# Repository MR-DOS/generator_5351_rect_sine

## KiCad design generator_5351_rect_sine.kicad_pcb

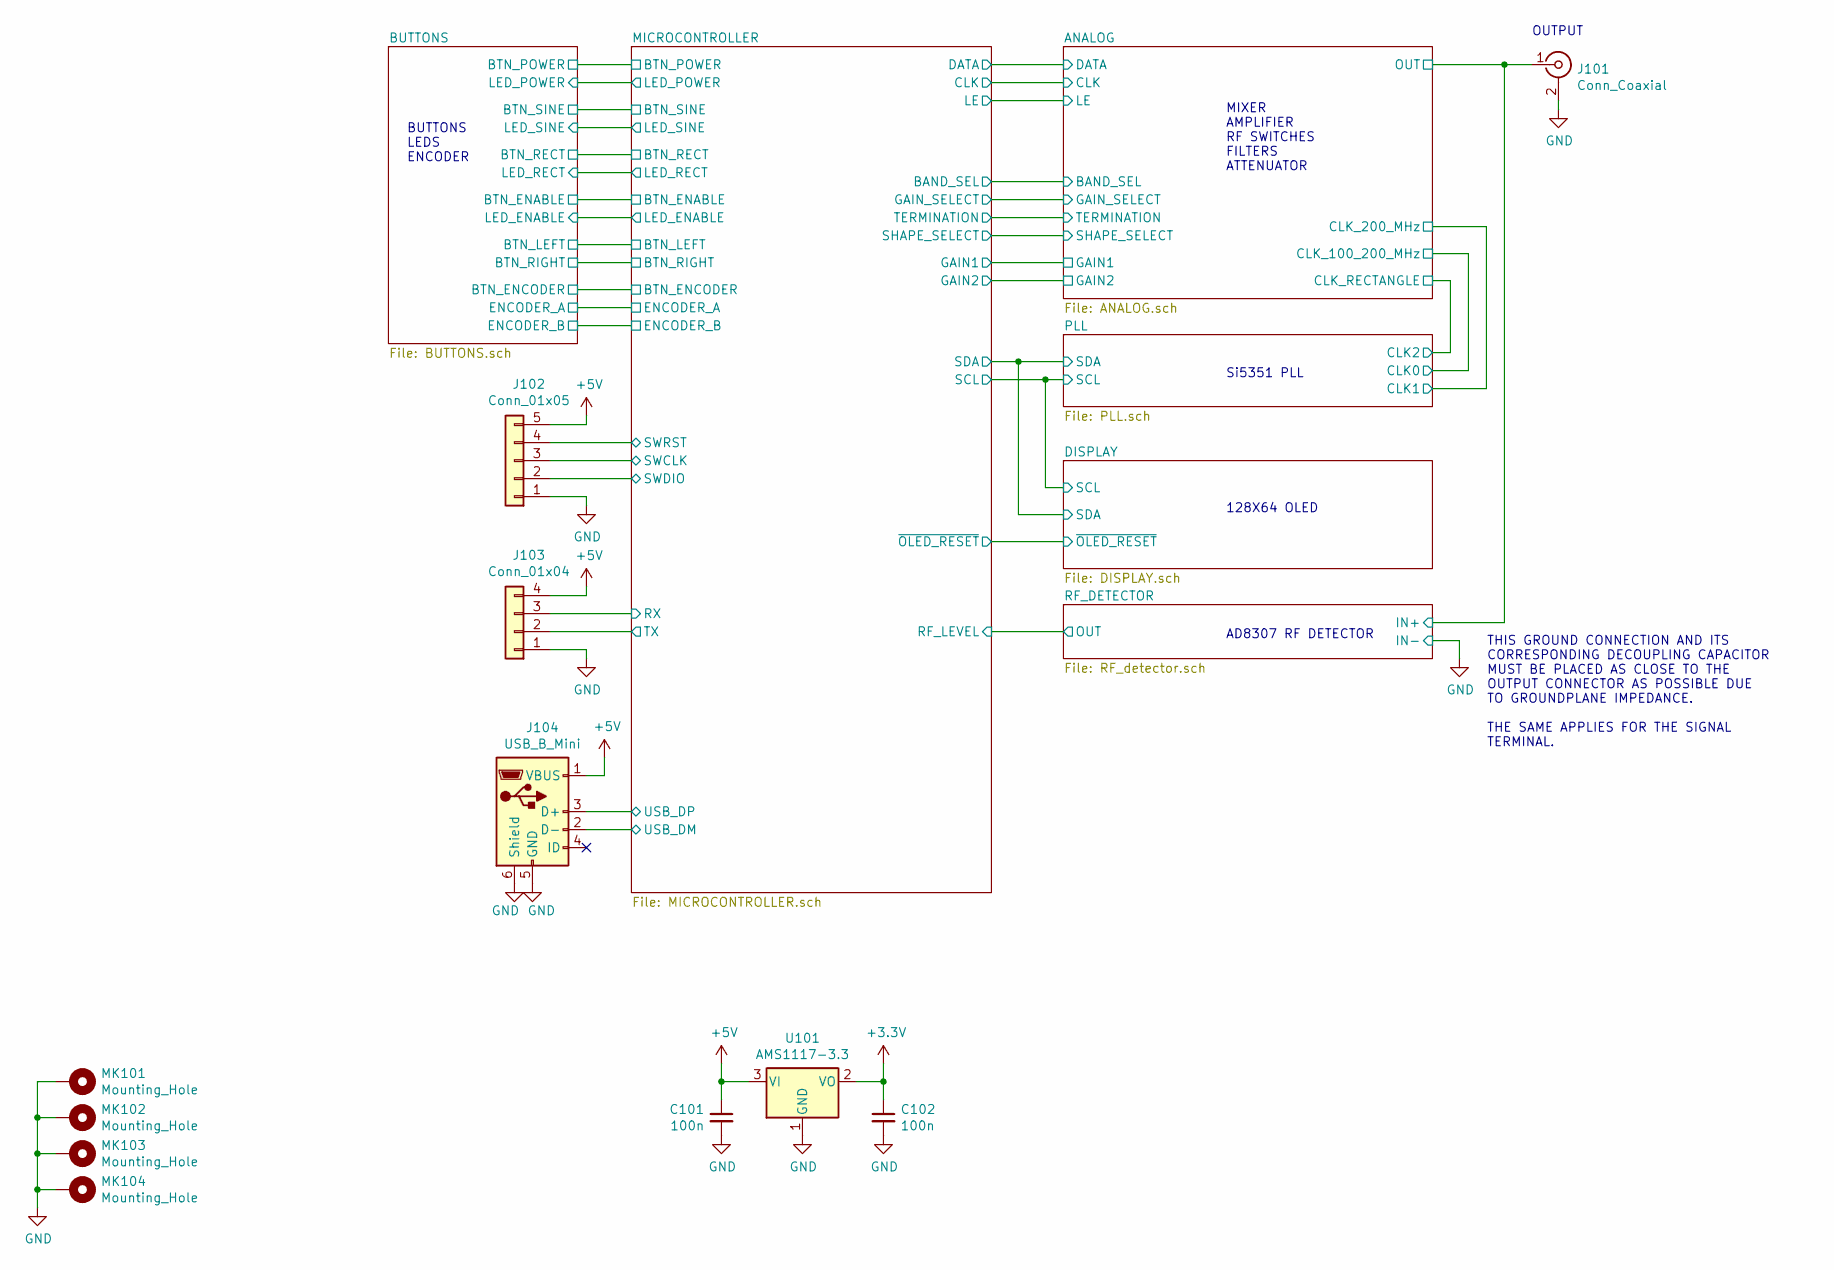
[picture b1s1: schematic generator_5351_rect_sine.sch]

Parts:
C101, C102: 100n; C_0805_2012Metric_Pad1.33x1.40mm_HandSolder
J101: Conn_Coaxial; Molex_SMA_Jack_Edge_Mount_Chinese
J102: Conn_01x05; JST_VH_B5PS-VH_1x05_P3.96mm_Horizontal
J103: Conn_01x04; JST_VH_B4PS-VH_1x04_P3.96mm_Horizontal
J104: USB_B_Mini; USB_Mini-B_Lumberg_2486_01_Horizontal
MK101, MK102, MK103, MK104: Mounting_Hole; MountingHole_3.2mm_M3_Pad
U101: AMS1117-3.3; SOT-223-3_TabPin2

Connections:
+5V: C101.1, J102.5, J103.4, J104.1 (VBUS), U101.3 (VI); also elsewhere on the board
/MICROCONTROLLER/RX: J103.3; also elsewhere on the board
/MICROCONTROLLER/SWCLK: J102.3; also elsewhere on the board
/MICROCONTROLLER/SWDIO: J102.2; also elsewhere on the board
/MICROCONTROLLER/SWRST: J102.4; also elsewhere on the board
/MICROCONTROLLER/TX: J103.2; also elsewhere on the board
/MICROCONTROLLER/USB_DM: J104.2 (D-); also elsewhere on the board
/MICROCONTROLLER/USB_DP: J104.3 (D+); also elsewhere on the board
/RF_DETECTOR/IN+: J101.1 (In); also elsewhere on the board
SW_GND: C101.2, C102.2, J101.2 (Ext), J102.1, J103.1, J104.5 (GND), J104.6 (Shield), MK101.1, MK102.1, MK103.1, MK104.1, U101.1 (GND); also elsewhere on the board

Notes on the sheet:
THIS GROUND CONNECTION AND ITS CORRESPONDING DECOUPLING CAPACITOR MUST BE PLACED AS CLOSE TO THE OUTPUT CONNECTOR AS POSSIBLE DUE TO GROUNDPLANE IMPEDANCE. THE SAME APPLIES FOR THE SIGNAL TERMINAL.
MIXER AMPLIFIER RF SWITCHES FILTERS ATTENUATOR
Si5351 PLL
128X64 OLED
AD8307 RF DETECTOR
OUTPUT
BUTTONS LEDS ENCODER

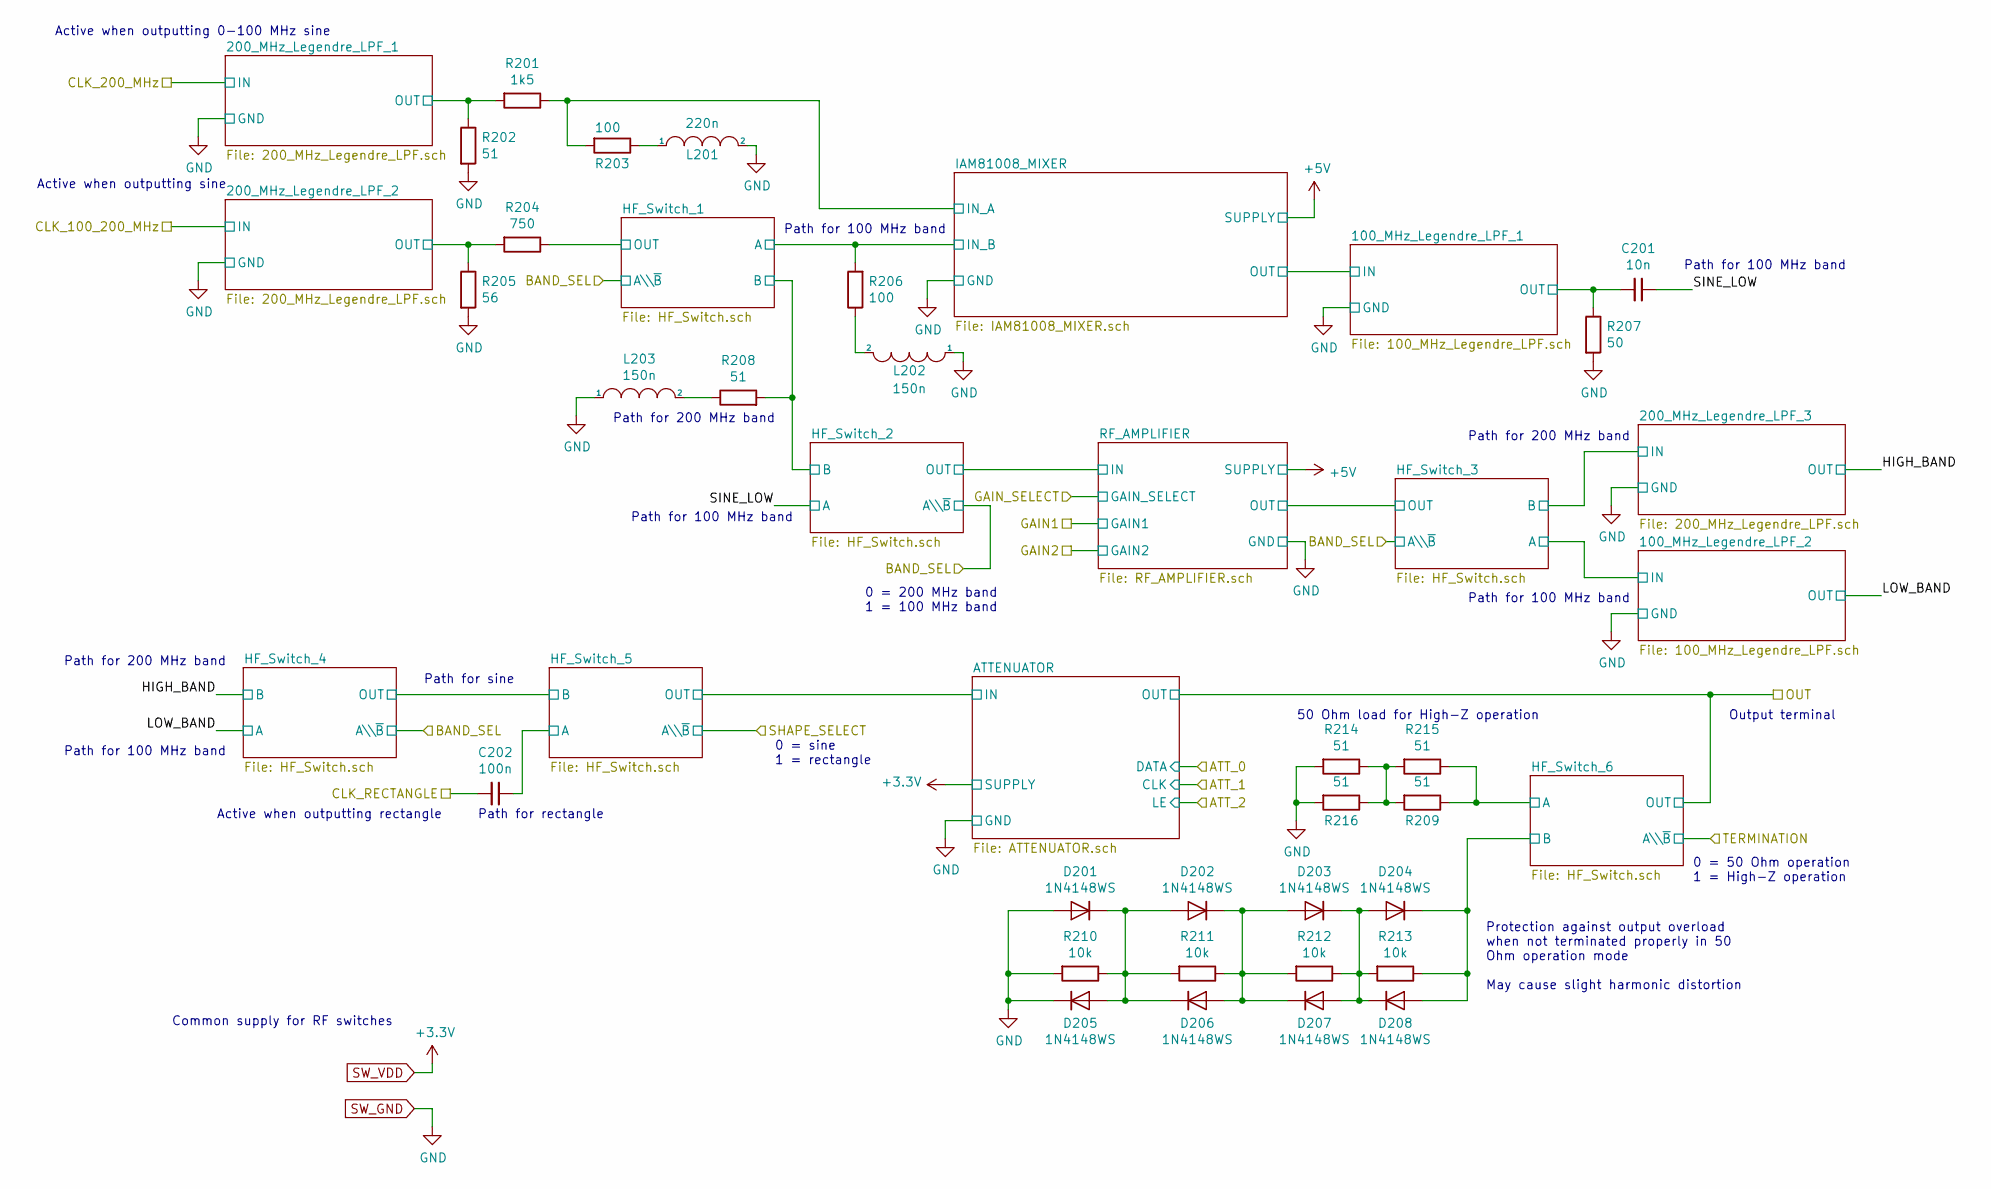
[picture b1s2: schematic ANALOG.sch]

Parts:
C201: 10n; C_0805_2012Metric_Pad1.33x1.40mm_HandSolder
C202: 100n; C_0805_2012Metric_Pad1.33x1.40mm_HandSolder
D201, D202, D203, D204, D205, D206, D207, D208: 1N4148WS; D_SOD-323
L201: 220n; L_0805_2012Metric_Pad1.33x1.40mm_HandSolder
L202, L203: 150n; L_0805_2012Metric_Pad1.33x1.40mm_HandSolder
R201: 1k5; R_0805_2012Metric_Pad1.33x1.40mm_HandSolder
R202, R208, R209, R214, R215, R216: 51; R_0805_2012Metric_Pad1.33x1.40mm_HandSolder
R203, R206: 100; R_0805_2012Metric_Pad1.33x1.40mm_HandSolder
R204: 750; R_0805_2012Metric_Pad1.33x1.40mm_HandSolder
R205: 56; R_0805_2012Metric_Pad1.33x1.40mm_HandSolder
R207: 50; R_0805_2012Metric_Pad1.33x1.40mm_HandSolder
R210, R211, R212, R213: 10k; R_0805_2012Metric_Pad1.33x1.40mm_HandSolder

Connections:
/ANALOG/100_MHz_Legendre_LPF_1/OUT: C201.2, R207.1; also elsewhere on the board
/ANALOG/200_MHz_Legendre_LPF_1/OUT: R201.2, R202.1; also elsewhere on the board
/ANALOG/200_MHz_Legendre_LPF_2/OUT: R204.2, R205.1; also elsewhere on the board
/ANALOG/HF_Switch_1/A: R206.2; also elsewhere on the board
/ANALOG/HF_Switch_1/B: R208.2; also elsewhere on the board
/ANALOG/HF_Switch_1/OUT: R204.1; also elsewhere on the board
/ANALOG/HF_Switch_5/A: C202.1; also elsewhere on the board
/ANALOG/HF_Switch_6/A: R209.1, R215.1; also elsewhere on the board
/ANALOG/HF_Switch_6/B: D204.1 (K), D208.2 (A), R213.1; also elsewhere on the board
/ANALOG/IAM81008_MIXER/IN_A: R201.1, R203.2; also elsewhere on the board
/ANALOG/SINE_LOW: C201.1; also elsewhere on the board
/PLL/CLK2: C202.2; also elsewhere on the board
unnamed: D201.1 (K), D202.2 (A), D205.2 (A), D206.1 (K), R210.1, R211.2
unnamed: D202.1 (K), D203.2 (A), D206.2 (A), D207.1 (K), R211.1, R212.2
unnamed: D203.1 (K), D204.2 (A), D207.2 (A), D208.1 (K), R212.1, R213.2
unnamed: L201.1, R203.1
unnamed: L202.2, R206.1
unnamed: L203.2, R208.1
unnamed: R209.2, R214.1, R215.2, R216.1
SW_GND: D201.2 (A), D205.1 (K), L201.2, L202.1, L203.1, R202.2, R205.2, R207.2, R210.2, R214.2, R216.2; also elsewhere on the board

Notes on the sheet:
Path for 100 MHz band
Path for 200 MHz band
Common supply for RF switches
Active when outputting 0-100 MHz sine
Active when outputting sine
0 = sine 1 = rectangle
Path for sine
Path for rectangle
Protection against output overload when not terminated properly in 50 Ohm operation mode May cause slight harmonic distortion
50 Ohm load for High-Z operation
0 = 50 Ohm operation 1 = High-Z operation
Output terminal
0 = 200 MHz band 1 = 100 MHz band
Active when outputting rectangle

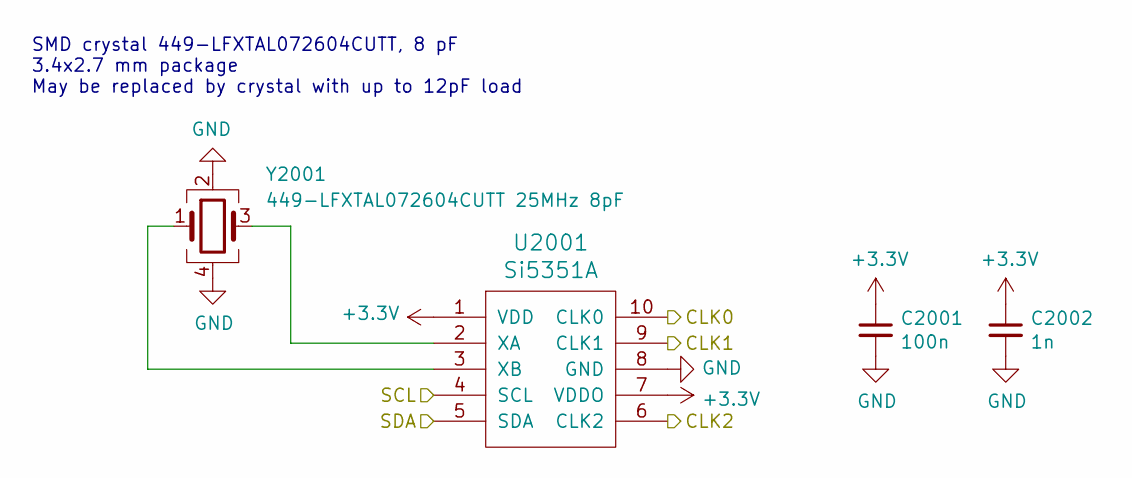
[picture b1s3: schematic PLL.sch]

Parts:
C2001: 100n; C_0805_2012Metric_Pad1.33x1.40mm_HandSolder
C2002: 1n; C_0805_2012Metric_Pad1.33x1.40mm_HandSolder
U2001: Si5351A; MSOP-10_3x3mm_P0.5mm
Y2001: 449-LFXTAL072604CUTT 25MHz 8pF; Crystal_SMD_3225-4Pin_3.2x2.5mm_HandSoldering

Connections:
/DISPLAY/SCL: U2001.4 (SCL); also elsewhere on the board
/DISPLAY/SDA: U2001.5 (SDA); also elsewhere on the board
/PLL/CLK0: U2001.10 (CLK0); also elsewhere on the board
/PLL/CLK1: U2001.9 (CLK1); also elsewhere on the board
/PLL/CLK2: U2001.6 (CLK2); also elsewhere on the board
unnamed: U2001.2 (XA), Y2001.3
unnamed: U2001.3 (XB), Y2001.1
SW_GND: C2001.2, C2002.2, U2001.8 (GND), Y2001.2, Y2001.4; also elsewhere on the board

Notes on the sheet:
SMD crystal 449-LFXTAL072604CUTT, 8 pF 3.4x2.7 mm package May be replaced by crystal with up to 12pF load

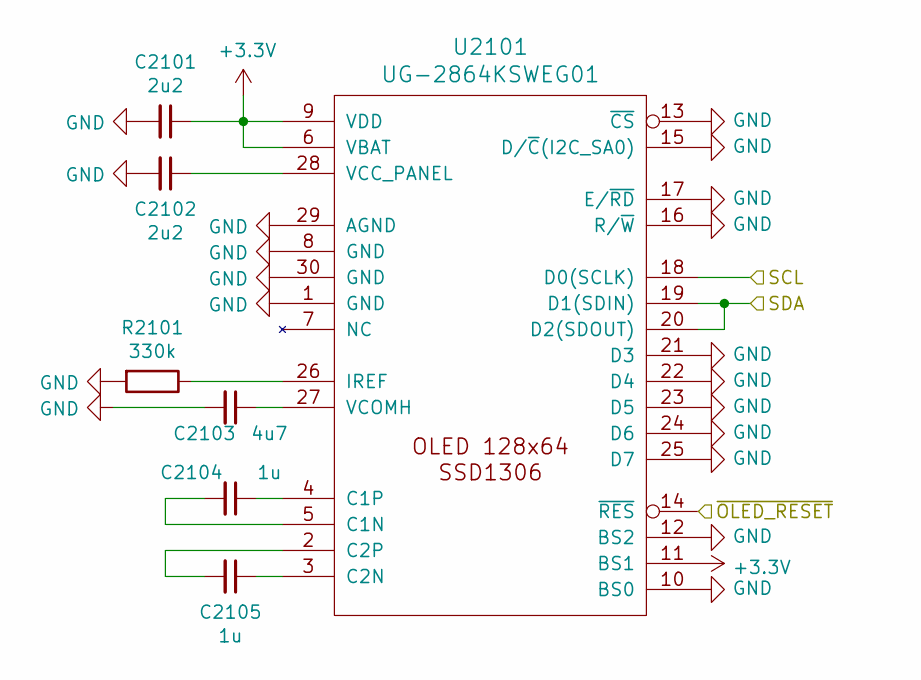
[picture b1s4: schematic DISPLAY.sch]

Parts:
C2101, C2102: 2u2; C_0805_2012Metric_Pad1.33x1.40mm_HandSolder
C2103: 4u7; C_0805_2012Metric_Pad1.33x1.40mm_HandSolder
C2104, C2105: 1u; C_0805_2012Metric_Pad1.33x1.40mm_HandSolder
R2101: 330k; R_0805_2012Metric_Pad1.33x1.40mm_HandSolder
U2101: UG-2864KSWEG01

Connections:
/DISPLAY/SCL: U2101.18 (D0(SCLK)); also elsewhere on the board
/DISPLAY/SDA: U2101.19 (D1(SDIN)), U2101.20 (D2(SDOUT)); also elsewhere on the board
/DISPLAY/~OLED_RESET: U2101.14 (~RES); also elsewhere on the board
unnamed: C2102.1, U2101.28 (VCC_PANEL)
unnamed: C2103.1, U2101.27 (VCOMH)
unnamed: C2104.1, U2101.4 (C1P)
unnamed: C2104.2, U2101.5 (C1N)
unnamed: C2105.1, U2101.3 (C2N)
unnamed: C2105.2, U2101.2 (C2P)
unnamed: R2101.1, U2101.26 (IREF)
SW_GND: C2101.2, C2102.2, C2103.2, R2101.2, U2101.1 (GND), U2101.8 (GND), U2101.10 (BS0), U2101.12 (BS2), U2101.13 (~CS), U2101.15 (D/~C~(I2C_SA0)), U2101.16 (R/~W), U2101.17 (E/~RD), U2101.21 (D3), U2101.22 (D4), U2101.23 (D5), U2101.24 (D6), U2101.25 (D7), U2101.29 (AGND), U2101.30 (GND); also elsewhere on the board

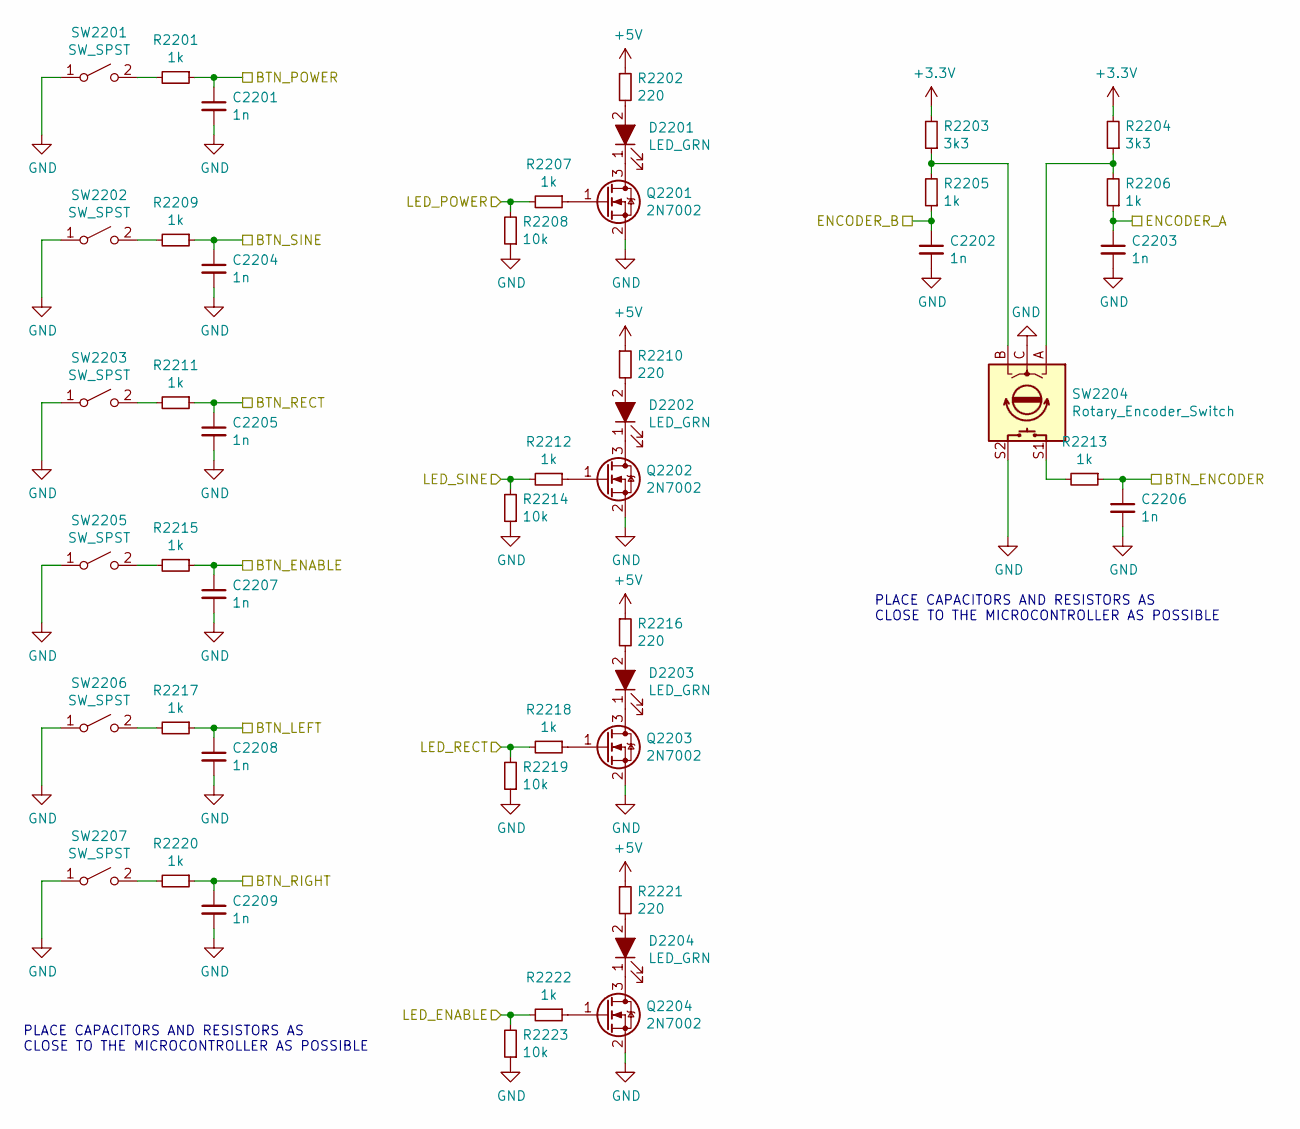
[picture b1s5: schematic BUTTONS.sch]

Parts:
C2201, C2202, C2203, C2204, C2205, C2206, C2207, C2208, C2209: 1n; C_0805_2012Metric_Pad1.33x1.40mm_HandSolder
D2201, D2202, D2203, D2204: LED_GRN; C_0603_1608Metric_Pad1.05x0.95mm_HandSolder
Q2201, Q2202, Q2203, Q2204: 2N7002; SOT-23_Handsoldering
R2201, R2205, R2206, R2207, R2209, R2211, R2212, R2213, R2215, R2217, R2218, R2220, R2222: 1k; R_0805_2012Metric_Pad1.33x1.40mm_HandSolder
R2202, R2210, R2216, R2221: 220; R_0805_2012Metric_Pad1.33x1.40mm_HandSolder
R2203, R2204: 3k3; R_0805_2012Metric_Pad1.33x1.40mm_HandSolder
R2208, R2214, R2219, R2223: 10k; R_0805_2012Metric_Pad1.33x1.40mm_HandSolder
SW2201, SW2202, SW2203, SW2205, SW2206, SW2207: SW_SPST; SW_SPST_TL3342
SW2204: Rotary_Encoder_Switch; RotaryEncoder_Alps_EC11E-Switch_Vertical_H20mm

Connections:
+5V: R2202.1, R2210.1, R2216.1, R2221.1; also elsewhere on the board
/BUTTONS/BTN_ENABLE: C2207.1, R2215.1; also elsewhere on the board
/BUTTONS/BTN_ENCODER: C2206.1, R2213.1; also elsewhere on the board
/BUTTONS/BTN_LEFT: C2208.1, R2217.1; also elsewhere on the board
/BUTTONS/BTN_POWER: C2201.1, R2201.1; also elsewhere on the board
/BUTTONS/BTN_RECT: C2205.1, R2211.1; also elsewhere on the board
/BUTTONS/BTN_RIGHT: C2209.1, R2220.1; also elsewhere on the board
/BUTTONS/BTN_SINE: C2204.1, R2209.1; also elsewhere on the board
/BUTTONS/ENCODER_A: C2203.1, R2206.1; also elsewhere on the board
/BUTTONS/ENCODER_B: C2202.1, R2205.1; also elsewhere on the board
/BUTTONS/LED_ENABLE: R2222.2, R2223.2; also elsewhere on the board
/BUTTONS/LED_POWER: R2207.2, R2208.2; also elsewhere on the board
/BUTTONS/LED_RECT: R2218.2, R2219.2; also elsewhere on the board
/BUTTONS/LED_SINE: R2212.2, R2214.2; also elsewhere on the board
unnamed: D2201.1 (K), Q2201.3 (D)
unnamed: D2201.2 (A), R2202.2
unnamed: D2202.1 (K), Q2202.3 (D)
unnamed: D2202.2 (A), R2210.2
unnamed: D2203.1 (K), Q2203.3 (D)
unnamed: D2203.2 (A), R2216.2
unnamed: D2204.1 (K), Q2204.3 (D)
unnamed: D2204.2 (A), R2221.2
unnamed: Q2201.1 (G), R2207.1
unnamed: Q2202.1 (G), R2212.1
unnamed: Q2203.1 (G), R2218.1
unnamed: Q2204.1 (G), R2222.1
unnamed: R2201.2, SW2201.2 (B)
unnamed: R2203.1, R2205.2, SW2204.B
unnamed: R2204.1, R2206.2, SW2204.A
unnamed: R2209.2, SW2202.2 (B)
unnamed: R2211.2, SW2203.2 (B)
unnamed: R2213.2, SW2204.S1
unnamed: R2215.2, SW2205.2 (B)
unnamed: R2217.2, SW2206.2 (B)
unnamed: R2220.2, SW2207.2 (B)
SW_GND: C2201.2, C2202.2, C2203.2, C2204.2, C2205.2, C2206.2, C2207.2, C2208.2, C2209.2, Q2201.2 (S), Q2202.2 (S), Q2203.2 (S), Q2204.2 (S), R2208.1, R2214.1, R2219.1, R2223.1, SW2201.1 (A), SW2202.1 (A), SW2203.1 (A), SW2204.C, SW2204.S2, SW2205.1 (A), SW2206.1 (A), SW2207.1 (A); also elsewhere on the board

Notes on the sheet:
PLACE CAPACITORS AND RESISTORS AS CLOSE TO THE MICROCONTROLLER AS POSSIBLE

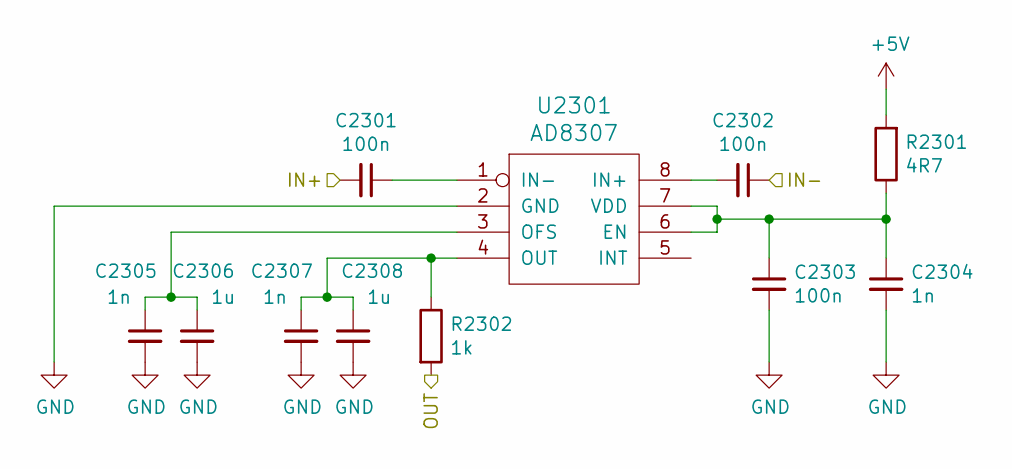
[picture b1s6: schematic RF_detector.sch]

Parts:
C2301, C2302, C2303: 100n; C_0805_2012Metric_Pad1.33x1.40mm_HandSolder
C2304, C2305, C2307: 1n; C_0805_2012Metric_Pad1.33x1.40mm_HandSolder
C2306, C2308: 1u; C_0805_2012Metric_Pad1.33x1.40mm_HandSolder
R2301: 4R7; R_0805_2012Metric_Pad1.33x1.40mm_HandSolder
R2302: 1k; R_0805_2012Metric_Pad1.33x1.40mm_HandSolder
U2301: AD8307; SOIC-8_3.9x4.9mm_P1.27mm

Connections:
+5V: R2301.2; also elsewhere on the board
/RF_DETECTOR/IN+: C2301.2; also elsewhere on the board
/RF_DETECTOR/OUT: R2302.2; also elsewhere on the board
unnamed: C2301.1, U2301.1 (IN-)
unnamed: C2302.2, U2301.8 (IN+)
unnamed: C2303.1, C2304.1, R2301.1, U2301.6 (EN), U2301.7 (VDD)
unnamed: C2305.1, C2306.1, U2301.3 (OFS)
unnamed: C2307.1, C2308.1, R2302.1, U2301.4 (OUT)
SW_GND: C2302.1, C2303.2, C2304.2, C2305.2, C2306.2, C2307.2, C2308.2, U2301.2 (GND); also elsewhere on the board

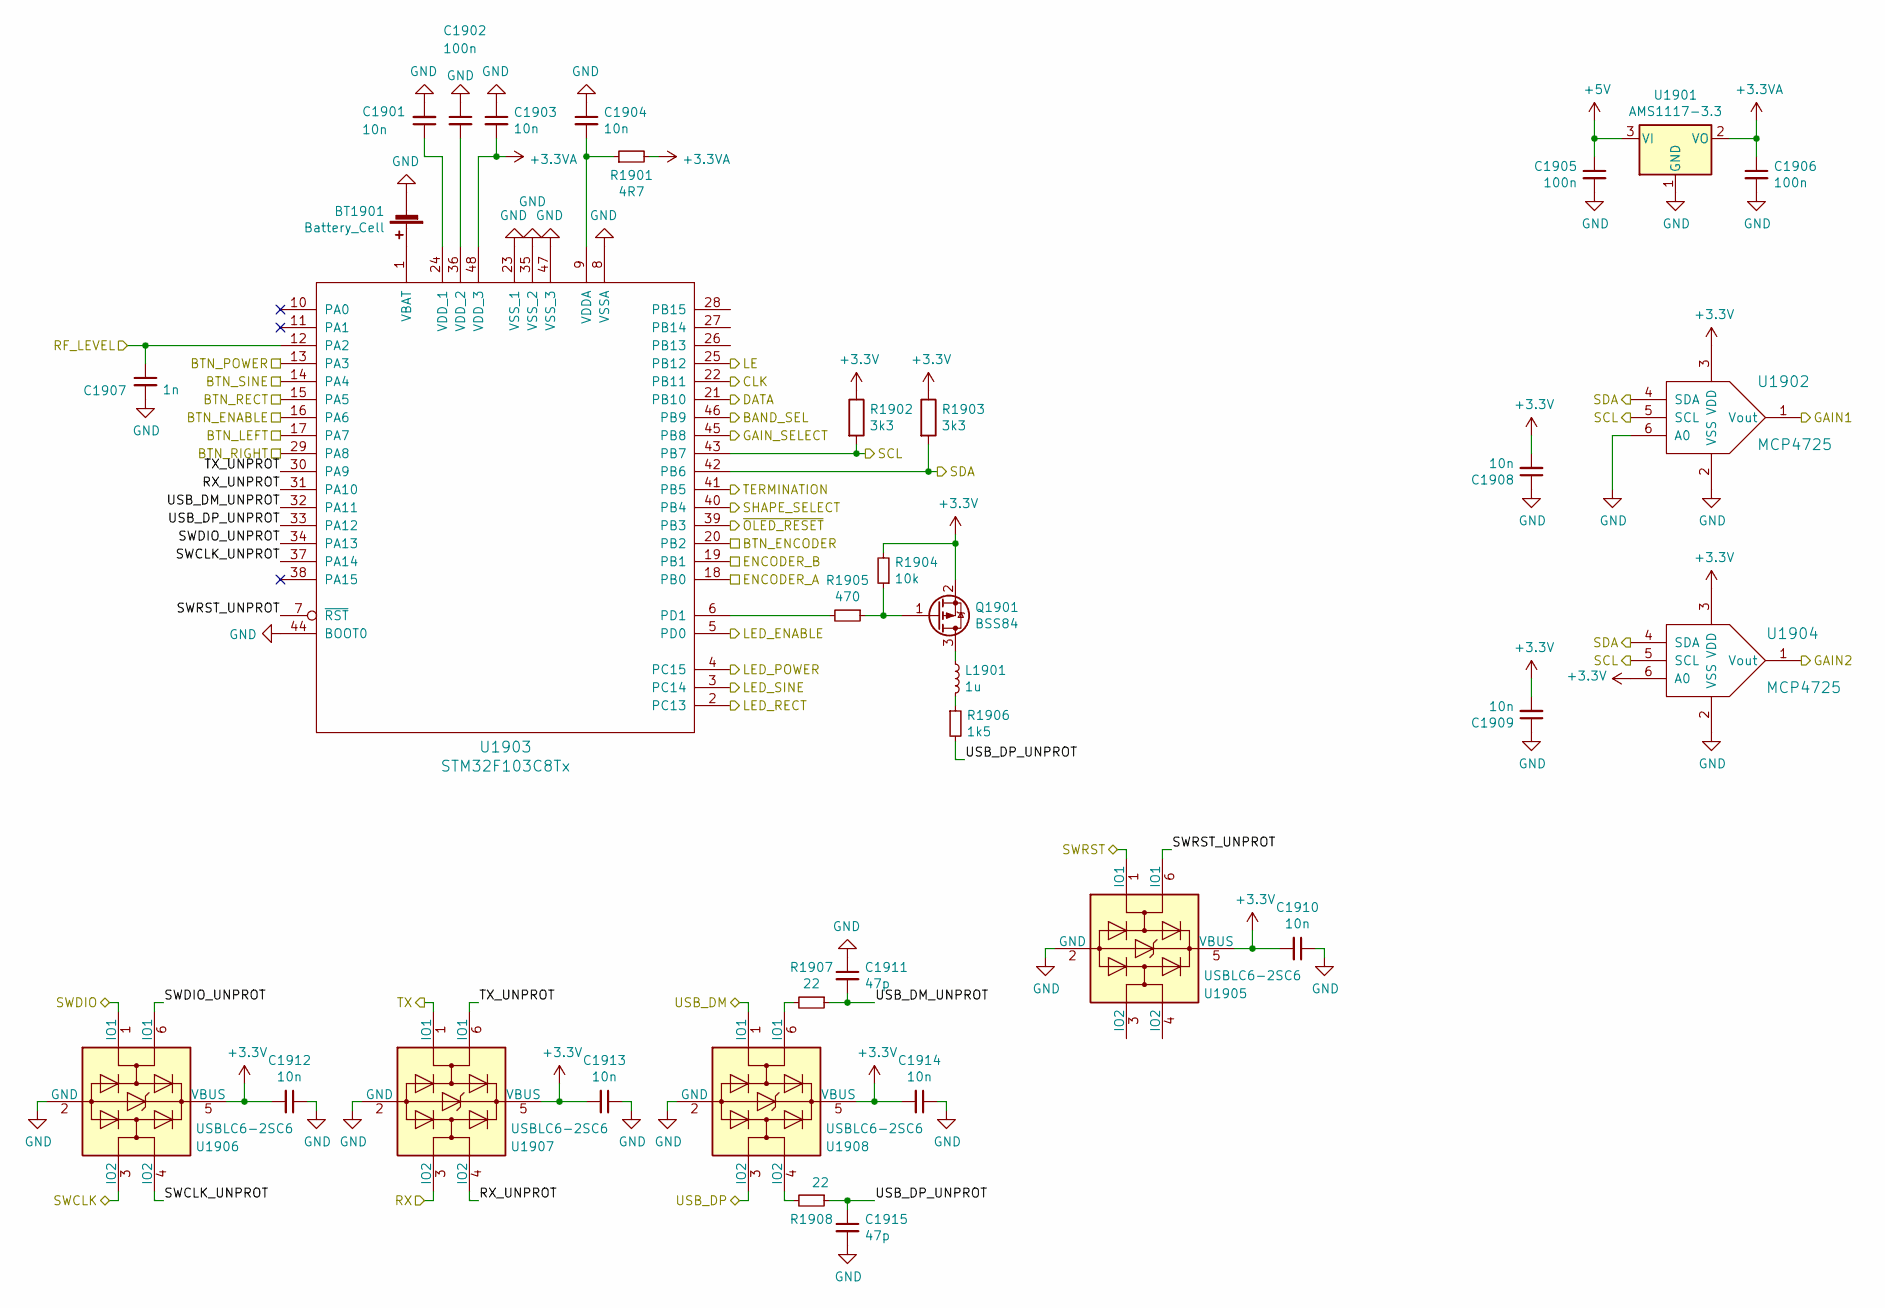
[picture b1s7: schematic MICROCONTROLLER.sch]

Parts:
BT1901: Battery_Cell; BatteryHolder_Keystone_3034_1x20mm
C1901, C1903, C1904, C1908, C1909, C1910, C1912, C1913, C1914: 10n; C_0805_2012Metric_Pad1.33x1.40mm_HandSolder
C1902, C1905, C1906: 100n; C_0805_2012Metric_Pad1.33x1.40mm_HandSolder
C1907: 1n; C_0805_2012Metric_Pad1.33x1.40mm_HandSolder
C1911, C1915: 47p; C_0805_2012Metric_Pad1.33x1.40mm_HandSolder
L1901: 1u; L_0805_2012Metric_Pad1.33x1.40mm_HandSolder
Q1901: BSS84; SOT-23_Handsoldering
R1901: 4R7; R_0805_2012Metric_Pad1.33x1.40mm_HandSolder
R1902, R1903: 3k3; R_0805_2012Metric_Pad1.33x1.40mm_HandSolder
R1904: 10k; R_0805_2012Metric_Pad1.33x1.40mm_HandSolder
R1905: 470; R_0805_2012Metric_Pad1.33x1.40mm_HandSolder
R1906: 1k5; R_0805_2012Metric_Pad1.33x1.40mm_HandSolder
R1907, R1908: 22; R_0805_2012Metric_Pad1.33x1.40mm_HandSolder
U1901: AMS1117-3.3; SOT-223-3_TabPin2
U1902, U1904: MCP4725; SOT-23-6_Handsoldering
U1903: STM32F103C8Tx; TQFP-48_7x7mm_P0.5mm
U1905, U1906, U1907, U1908: USBLC6-2SC6; SOT-23-6

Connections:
+3.3VA: C1903.2, C1906.1, R1901.2, U1901.2 (VO), U1903.48 (VDD_3)
+5V: C1905.1, U1901.3 (VI); also elsewhere on the board
/ANALOG/BAND_SEL: U1903.46 (PB9); also elsewhere on the board
/ANALOG/GAIN1: U1902.1 (Vout); also elsewhere on the board
/ANALOG/GAIN2: U1904.1 (Vout); also elsewhere on the board
/ANALOG/GAIN_SELECT: U1903.45 (PB8); also elsewhere on the board
/ANALOG/SHAPE_SELECT: U1903.40 (PB4); also elsewhere on the board
/ANALOG/TERMINATION: U1903.41 (PB5); also elsewhere on the board
/BUTTONS/BTN_ENABLE: U1903.16 (PA6); also elsewhere on the board
/BUTTONS/BTN_ENCODER: U1903.20 (PB2); also elsewhere on the board
/BUTTONS/BTN_LEFT: U1903.17 (PA7); also elsewhere on the board
/BUTTONS/BTN_POWER: U1903.13 (PA3); also elsewhere on the board
/BUTTONS/BTN_RECT: U1903.15 (PA5); also elsewhere on the board
/BUTTONS/BTN_RIGHT: U1903.29 (PA8); also elsewhere on the board
/BUTTONS/BTN_SINE: U1903.14 (PA4); also elsewhere on the board
/BUTTONS/ENCODER_A: U1903.18 (PB0); also elsewhere on the board
/BUTTONS/ENCODER_B: U1903.19 (PB1); also elsewhere on the board
/BUTTONS/LED_ENABLE: U1903.5 (PD0); also elsewhere on the board
/BUTTONS/LED_POWER: U1903.4 (PC15); also elsewhere on the board
/BUTTONS/LED_RECT: U1903.2 (PC13); also elsewhere on the board
/BUTTONS/LED_SINE: U1903.3 (PC14); also elsewhere on the board
/DISPLAY/SCL: R1902.2, U1902.5 (SCL), U1903.43 (PB7), U1904.5 (SCL); also elsewhere on the board
/DISPLAY/SDA: R1903.2, U1902.4 (SDA), U1903.42 (PB6), U1904.4 (SDA); also elsewhere on the board
/DISPLAY/~OLED_RESET: U1903.39 (PB3); also elsewhere on the board
/MICROCONTROLLER/CLK: U1903.22 (PB11)
/MICROCONTROLLER/DATA: U1903.21 (PB10)
/MICROCONTROLLER/LE: U1903.25 (PB12)
/MICROCONTROLLER/RX: U1907.3 (IO2); also elsewhere on the board
/MICROCONTROLLER/RX_UNPROT: U1903.31 (PA10), U1907.4 (IO2)
/MICROCONTROLLER/SWCLK: U1906.3 (IO2); also elsewhere on the board
/MICROCONTROLLER/SWCLK_UNPROT: U1903.37 (PA14), U1906.4 (IO2)
/MICROCONTROLLER/SWDIO: U1906.1 (IO1); also elsewhere on the board
/MICROCONTROLLER/SWDIO_UNPROT: U1903.34 (PA13), U1906.6 (IO1)
/MICROCONTROLLER/SWRST: U1905.1 (IO1); also elsewhere on the board
/MICROCONTROLLER/SWRST_UNPROT: U1903.7 (~RST), U1905.6 (IO1)
/MICROCONTROLLER/TX: U1907.1 (IO1); also elsewhere on the board
/MICROCONTROLLER/TX_UNPROT: U1903.30 (PA9), U1907.6 (IO1)
/MICROCONTROLLER/USB_DM: U1908.1 (IO1); also elsewhere on the board
/MICROCONTROLLER/USB_DM_UNPROT: C1911.2, R1907.1, U1903.32 (PA11)
/MICROCONTROLLER/USB_DP: U1908.3 (IO2); also elsewhere on the board
/MICROCONTROLLER/USB_DP_UNPROT: C1915.1, R1906.2, R1908.1, U1903.33 (PA12)
/RF_DETECTOR/OUT: C1907.1, U1903.12 (PA2); also elsewhere on the board
unnamed: BT1901.1 (+), U1903.1 (VBAT)
unnamed: C1901.1, U1903.24 (VDD_1)
unnamed: C1902.2, U1903.36 (VDD_2)
unnamed: C1904.2, R1901.1, U1903.9 (VDDA)
unnamed: L1901.1, Q1901.3 (D)
unnamed: L1901.2, R1906.1
unnamed: Q1901.1 (G), R1904.1, R1905.1
unnamed: R1905.2, U1903.6 (PD1)
unnamed: R1907.2, U1908.6 (IO1)
unnamed: R1908.2, U1908.4 (IO2)
SW_GND: BT1901.2 (-), C1901.2, C1902.1, C1903.1, C1904.1, C1905.2, C1906.2, C1907.2, C1908.1, C1909.1, C1910.1, C1911.1, C1912.1, C1913.1, C1914.1, C1915.2, U1901.1 (GND), U1902.2 (VSS), U1902.6 (A0), U1903.8 (VSSA), U1903.23 (VSS_1), U1903.35 (VSS_2), U1903.44 (BOOT0), U1903.47 (VSS_3), U1904.2 (VSS), U1905.2 (GND), U1906.2 (GND), U1907.2 (GND), U1908.2 (GND); also elsewhere on the board

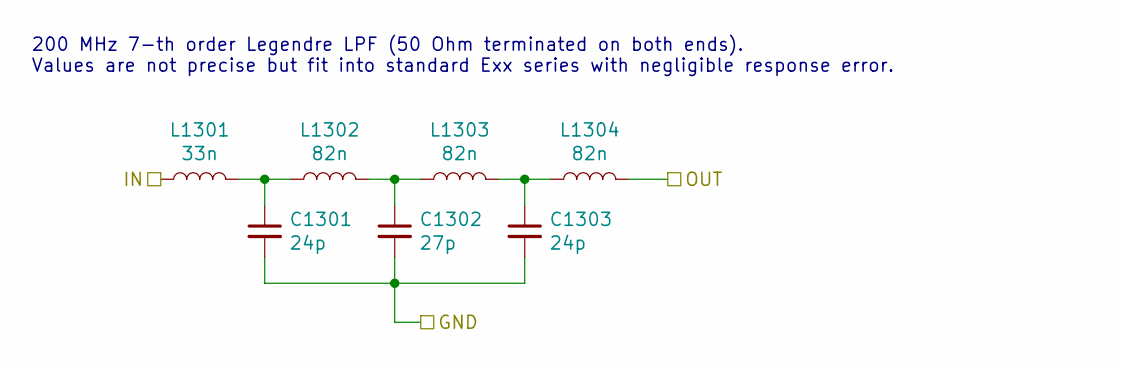
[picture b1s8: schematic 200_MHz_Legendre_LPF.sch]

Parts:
C301, C303: 24p; C_0805_2012Metric_Pad1.33x1.40mm_HandSolder
C302: 27p; C_0805_2012Metric_Pad1.33x1.40mm_HandSolder
L301: 33n; L_0805_2012Metric_Pad1.33x1.40mm_HandSolder
L302, L303, L304: 82n; L_0805_2012Metric_Pad1.33x1.40mm_HandSolder

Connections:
/ANALOG/200_MHz_Legendre_LPF_1/OUT: L304.2; also elsewhere on the board
/PLL/CLK1: L301.1; also elsewhere on the board
unnamed: C301.1, L301.2, L302.1
unnamed: C302.1, L302.2, L303.1
unnamed: C303.1, L303.2, L304.1
SW_GND: C301.2, C302.2, C303.2; also elsewhere on the board

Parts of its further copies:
C401, C403, C1301, C1303: 24p; C_0805_2012Metric_Pad1.33x1.40mm_HandSolder
C402, C1302: 27p; C_0805_2012Metric_Pad1.33x1.40mm_HandSolder
L401, L1301: 33n; L_0805_2012Metric_Pad1.33x1.40mm_HandSolder
L402, L403, L404, L1302, L1303, L1304: 82n; L_0805_2012Metric_Pad1.33x1.40mm_HandSolder

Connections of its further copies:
/ANALOG/200_MHz_Legendre_LPF_2/OUT: L404.2; also elsewhere on the board
/ANALOG/HF_Switch_3/B: L1301.1; also elsewhere on the board
/ANALOG/HIGH_BAND: L1304.2; also elsewhere on the board
/PLL/CLK0: L401.1; also elsewhere on the board
unnamed: C401.1, L401.2, L402.1
unnamed: C402.1, L402.2, L403.1
unnamed: C403.1, L403.2, L404.1
unnamed: C1301.1, L1301.2, L1302.1
unnamed: C1302.1, L1302.2, L1303.1
unnamed: C1303.1, L1303.2, L1304.1
SW_GND: C401.2, C402.2, C403.2, C1301.2, C1302.2, C1303.2; also elsewhere on the board

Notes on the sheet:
200 MHz 7-th order Legendre LPF (50 Ohm terminated on both ends). Values are not precise but fit into standard Exx series with negligible response error.

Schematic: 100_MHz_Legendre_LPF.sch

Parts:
C501, C502, C504: 47p; C_0805_2012Metric_Pad1.33x1.40mm_HandSolder
C503: 6p8; C_0805_2012Metric_Pad1.33x1.40mm_HandSolder
C505: 3p3; C_0805_2012Metric_Pad1.33x1.40mm_HandSolder
L501: 68n; L_0805_2012Metric_Pad1.33x1.40mm_HandSolder
L502, L503, L505: 150n; L_0805_2012Metric_Pad1.33x1.40mm_HandSolder
L504: 33n; L_0805_2012Metric_Pad1.33x1.40mm_HandSolder

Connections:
/ANALOG/100_MHz_Legendre_LPF_1/IN: L501.1; also elsewhere on the board
/ANALOG/100_MHz_Legendre_LPF_1/OUT: L505.2; also elsewhere on the board
unnamed: C501.1, L501.2, L502.1
unnamed: C502.1, C503.1, L502.2, L503.1
unnamed: C504.1, C505.1, L504.2, L505.1
unnamed: L503.2, L504.1
SW_GND: C501.2, C502.2, C503.2, C504.2, C505.2; also elsewhere on the board

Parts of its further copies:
C901, C902, C904: 47p; C_0805_2012Metric_Pad1.33x1.40mm_HandSolder
C903: 6p8; C_0805_2012Metric_Pad1.33x1.40mm_HandSolder
C905: 3p3; C_0805_2012Metric_Pad1.33x1.40mm_HandSolder
L901: 68n; L_0805_2012Metric_Pad1.33x1.40mm_HandSolder
L902, L903, L905: 150n; L_0805_2012Metric_Pad1.33x1.40mm_HandSolder
L904: 33n; L_0805_2012Metric_Pad1.33x1.40mm_HandSolder

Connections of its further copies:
/ANALOG/HF_Switch_3/A: L901.1; also elsewhere on the board
/ANALOG/LOW_BAND: L905.2; also elsewhere on the board
unnamed: C901.1, L901.2, L902.1
unnamed: C902.1, C903.1, L902.2, L903.1
unnamed: C904.1, C905.1, L904.2, L905.1
unnamed: L903.2, L904.1
SW_GND: C901.2, C902.2, C903.2, C904.2, C905.2; also elsewhere on the board

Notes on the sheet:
100 MHz 7-th order Legendre LPF (50 Ohm terminated on both ends). Values are not precise but fit into standard Exx series with negligible response error.
